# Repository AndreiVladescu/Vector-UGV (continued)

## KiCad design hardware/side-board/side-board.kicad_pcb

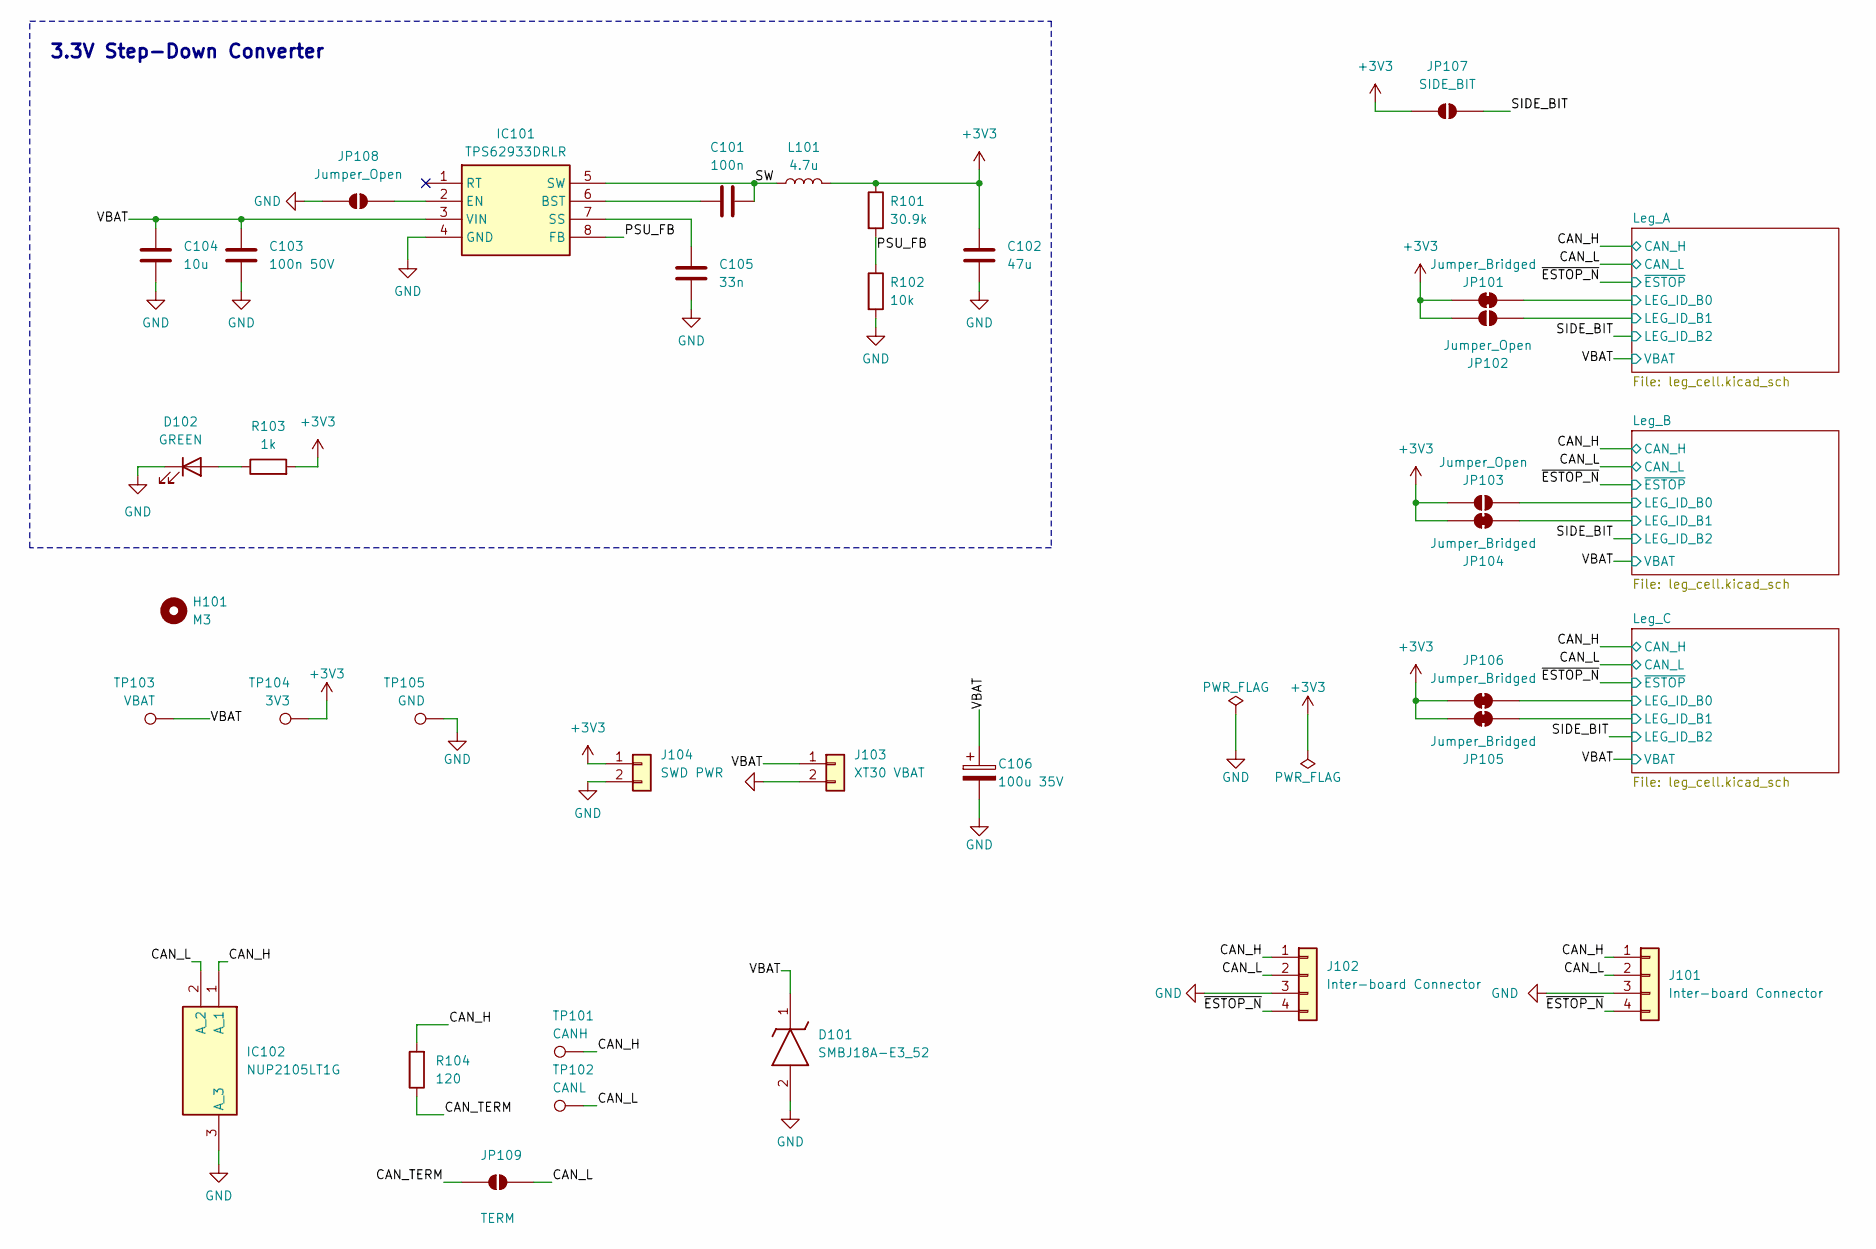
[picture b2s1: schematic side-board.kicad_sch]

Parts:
C101: 100n; C_0402_1005Metric
C102: 47u; C_0805_2012Metric
C103: 100n 50V; C_0402_1005Metric
C104: 10u; C_0603_1608Metric
C105: 33n; C_0402_1005Metric
C106: 100u 35V; CP_Elec_8x10.5
D101: SMBJ18A-E3_52; DIOM5436X244N; Mouser Part Number 625-SMBJ18A-E3
D102: GREEN; LED_0805_2012Metric
H101: M3; MountingHole_3.2mm_M3_DIN965_Pad_TopBottom
IC101: TPS62933DRLR; SOTFL50P160X60-8N; Mouser Part Number 595-TPS62933DRLR
IC102: NUP2105LT1G; SOT96P237X111-3N; Mouser Part Number 863-NUP2105LT1G
J101: Inter-board Connector; PinHeader_1x04_P2.54mm_Vertical_Tile
J102: Inter-board Connector; JST_XH_B4B-XH-A_1x04_P2.50mm_Vertical
J103: XT30 VBAT; AMASS_XT30U-M_1x02_P5.0mm_Vertical
J104: SWD PWR; PinHeader_1x02_P2.54mm_Vertical
JP101, JP104, JP105, JP106: Jumper_Bridged; SolderJumper-2_P1.3mm_Bridged2Bar_Pad1.0x1.5mm
JP102, JP103, JP108: Jumper_Open; SolderJumper-2_P1.3mm_Open_Pad1.0x1.5mm
JP107: SIDE_BIT; SolderJumper-2_P1.3mm_Open_Pad1.0x1.5mm
JP109: TERM; SolderJumper-2_P1.3mm_Open_Pad1.0x1.5mm
L101: 4.7u; INDPM4441X200N; Manufacturer_Part_Number SRP4020TA-4R7M
R101: 30.9k; R_0402_1005Metric
R102: 10k; R_0402_1005Metric
R103: 1k; R_0402_1005Metric
R104: 120; R_0402_1005Metric
TP101: CANH; TestPoint_Pad_D1.0mm
TP102: CANL; TestPoint_Pad_D1.0mm
TP103: VBAT; TestPoint_Pad_D1.0mm
TP104: 3V3; TestPoint_Pad_D1.0mm
TP105: GND; TestPoint_Pad_D1.0mm

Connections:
+3V3: C102.2, J104.1, JP101.1 (A), JP102.2 (B), JP103.1 (A), JP104.1 (A), JP105.1 (A), JP106.1 (A), JP107.1 (A), L101.2, R101.1, R103.2, TP104.1 (1_1); also elsewhere on the board
/CAN_H: IC102.1 (A_1), J101.1, J102.1, R104.2, TP101.1 (1_1); also elsewhere on the board
/CAN_L: IC102.2 (A_2), J101.2, J102.2, JP109.2 (B), TP102.1 (1_1); also elsewhere on the board
/CAN_TERM: JP109.1 (A), R104.1
/Leg_A/LEG_ID_B0: JP101.2 (B); also elsewhere on the board
/Leg_A/LEG_ID_B1: JP102.1 (A); also elsewhere on the board
/Leg_B/LEG_ID_B0: JP103.2 (B); also elsewhere on the board
/Leg_B/LEG_ID_B1: JP104.2 (B); also elsewhere on the board
/Leg_C/LEG_ID_B0: JP106.2 (B); also elsewhere on the board
/Leg_C/LEG_ID_B1: JP105.2 (B); also elsewhere on the board
/PSU_FB: IC101.8 (FB), R101.2, R102.1
/SIDE_BIT: JP107.2 (B); also elsewhere on the board
/SW: C101.2, IC101.5 (SW), L101.1
/VBAT: C103.2, C104.2, C106.1, D101.1 (K), IC101.3 (VIN), J103.1, TP103.1 (1_1); also elsewhere on the board
/~ESTOP_N: J101.4, J102.4; also elsewhere on the board
GND: C102.1, C103.1, C104.1, C105.1, C106.2, D101.2 (A), D102.1 (K), IC101.4 (GND), IC102.3 (A_3), J101.3, J102.3, J103.2, J104.2, JP108.1 (A), R102.2, TP105.1 (1_1); also elsewhere on the board
unnamed: D102.2 (A), R103.1
unnamed: C101.1, IC101.6 (BST)
unnamed: IC101.2 (EN), JP108.2 (B)
unnamed: C105.2, IC101.7 (SS)

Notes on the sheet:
3.3V Step-Down Converter

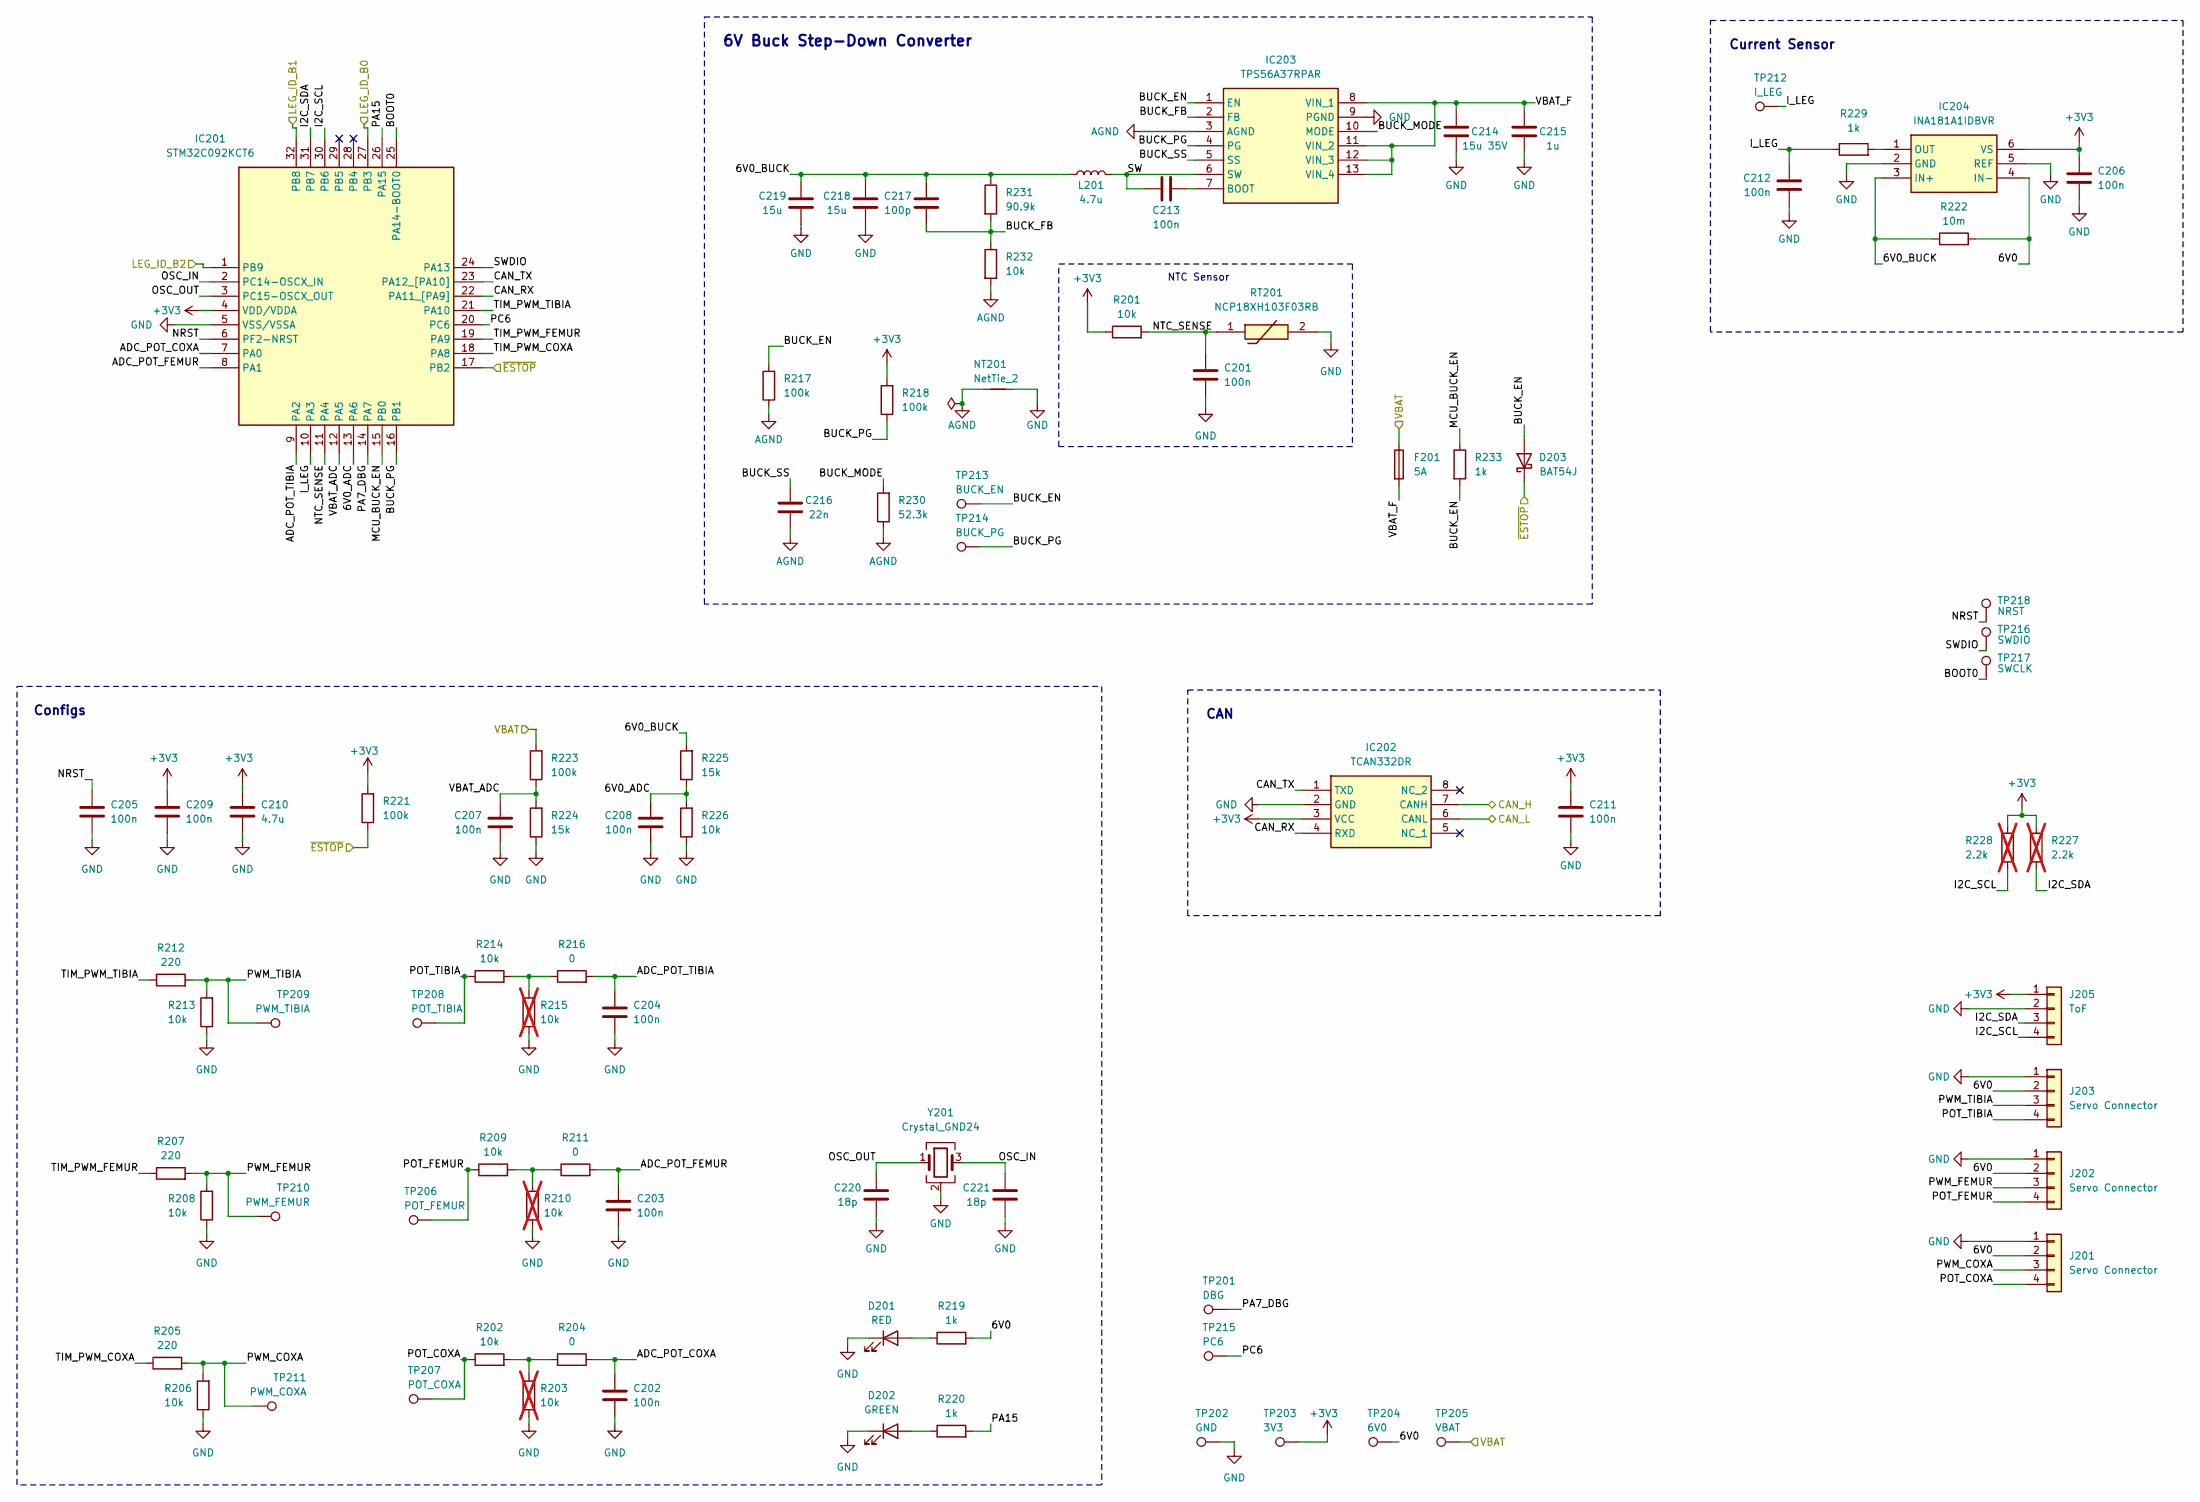
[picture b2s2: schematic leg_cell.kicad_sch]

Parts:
C201, C202, C203, C204, C205, C206, C207, C208, C209, C211, C212, C213: 100n; C_0402_1005Metric
C210: 4.7u; C_0805_2012Metric
C214: 15u 35V; C_1206_3216Metric
C215: 1u; C_0805_2012Metric
C216: 22n; C_0402_1005Metric
C217: 100p; C_0402_1005Metric
C218, C219: 15u; C_1206_3216Metric
C220, C221: 18p; C_0402_1005Metric
D201: RED; LED_0805_2012Metric
D202: GREEN; LED_0805_2012Metric
D203: BAT54J; D_SOD-323F
F201: 5A; Fuse_1206_3216Metric
IC201: STM32C092KCT6; QFP80P900X900X160-32N; Mouser Part Number 511-STM32C092KCT6
IC202: TCAN332DR; SOIC127P600X175-8N; Mouser Part Number 595-TCAN332DR
IC203: TPS56A37RPAR; Mouser Part Number 595-TPS56A37RPAR
IC204: INA181A1IDBVR; SOT95P280X145-6N; Mouser Part Number 595-INA181A1IDBVR
J201, J202, J203: Servo Connector; PinHeader_1x04_P2.54mm_Vertical_Tile
J205: ToF; PinHeader_1x04_P2.54mm_Vertical_Tile
L201: 4.7u; INDPM7973X540N; Manufacturer_Part_Number SRP7050WA-4R7M
NT201: NetTie_2; NetTie-2_SMD_Pad0.5mm
R201, R202, R206, R208, R209, R213, R214, R226, R232: 10k; R_0402_1005Metric
R203, R210, R215: 10k; R_0402_1005Metric; not fitted
R204, R211, R216: 0; R_0402_1005Metric
R205, R207, R212: 220; R_0402_1005Metric
R217, R218, R221, R223: 100k; R_0402_1005Metric
R219, R220, R229, R233: 1k; R_0402_1005Metric
R222: 10m; R_2512_6332Metric
R224, R225: 15k; R_0402_1005Metric
R227, R228: 2.2k; R_0402_1005Metric; not fitted
R230: 52.3k; R_0402_1005Metric
R231: 90.9k; R_0402_1005Metric
RT201: NCP18XH103F03RB; THRMC1608X95N; Mouser Part Number 81-NCP18XH103F03RB
TP201: DBG; TestPoint_Pad_D1.0mm
TP202: GND; TestPoint_Pad_D1.0mm
TP203: 3V3; TestPoint_Pad_D1.0mm
TP204: 6V0; TestPoint_Pad_D1.0mm
TP205: VBAT; TestPoint_Pad_D1.0mm
TP206: POT_FEMUR; TestPoint_Pad_D1.0mm
TP207: POT_COXA; TestPoint_Pad_D1.0mm
TP208: POT_TIBIA; TestPoint_Pad_D1.0mm
TP209: PWM_TIBIA; TestPoint_Pad_D1.0mm
TP210: PWM_FEMUR; TestPoint_Pad_D1.0mm
TP211: PWM_COXA; TestPoint_Pad_D1.0mm
TP212: I_LEG; TestPoint_Pad_D1.0mm
TP213: BUCK_EN; TestPoint_Pad_D1.0mm
TP214: BUCK_PG; TestPoint_Pad_D1.0mm
TP215: PC6; TestPoint_Pad_D1.0mm
TP216: SWDIO; TestPoint_Pad_D1.0mm
TP217: SWCLK; TestPoint_Pad_D1.0mm
TP218: NRST; TestPoint_Pad_D1.0mm
Y201: Crystal_GND24; Crystal_SMD_2016-4Pin_2.0x1.6mm; Manufacturer_Part_Number K2B400001210

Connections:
+3V3: C206.2, C209.2, C210.2, C211.2, IC201.4 (VDD/VDDA), IC202.3 (VCC), IC204.6 (VS), J205.1, R201.1, R218.2, R221.2, R227.2, R228.1, TP203.1 (1_1); also elsewhere on the board
/CAN_H: IC202.7 (CANH); also elsewhere on the board
/CAN_L: IC202.6 (CANL); also elsewhere on the board
/Leg_A/6V0: IC204.4 (IN-), J201.2, J202.2, J203.2, R219.2, R222.2, TP204.1 (1_1)
/Leg_A/6V0_ADC: C208.1, IC201.13 (PA6), R225.1, R226.2
/Leg_A/6V0_BUCK: C217.2, C218.2, C219.2, IC204.3 (IN+), L201.1, R222.1, R225.2, R231.1
/Leg_A/ADC_POT_COXA: C202.1, IC201.7 (PA0), R204.1
/Leg_A/ADC_POT_FEMUR: C203.1, IC201.8 (PA1), R211.2
/Leg_A/ADC_POT_TIBIA: C204.1, IC201.9 (PA2), R216.2
/Leg_A/AGND: C216.2, IC203.3 (AGND), NT201.1, R217.1, R230.1, R232.2
/Leg_A/BOOT0: IC201.25 (PA14-BOOT0), TP217.1 (1_1)
/Leg_A/BUCK_EN: D203.2 (A), IC203.1 (EN), R217.2, R233.2, TP213.1 (1_1)
/Leg_A/BUCK_FB: C217.1, IC203.2 (FB), R231.2, R232.1
/Leg_A/BUCK_MODE: IC203.10 (MODE), R230.2
/Leg_A/BUCK_PG: IC201.16 (PB1), IC203.4 (PG), R218.1, TP214.1 (1_1)
/Leg_A/BUCK_SS: C216.1, IC203.5 (SS)
/Leg_A/CAN_RX: IC201.22 (PA11_[PA9]), IC202.4 (RXD)
/Leg_A/CAN_TX: IC201.23 (PA12_[PA10]), IC202.1 (TXD)
/Leg_A/I2C_SCL: IC201.30 (PB6), J205.4, R228.2
/Leg_A/I2C_SDA: IC201.31 (PB7), J205.3, R227.1
/Leg_A/I_LEG: C212.1, IC201.10 (PA3), R229.1, TP212.1 (1_1)
/Leg_A/LEG_ID_B0: IC201.27 (PB3); also elsewhere on the board
/Leg_A/LEG_ID_B1: IC201.32 (PB8); also elsewhere on the board
/Leg_A/MCU_BUCK_EN: IC201.15 (PB0), R233.1
/Leg_A/NRST: C205.2, IC201.6 (PF2-NRST), TP218.1 (1_1)
/Leg_A/NTC_SENSE: C201.1, IC201.11 (PA4), R201.2, RT201.1
/Leg_A/OSC_IN: C221.2, IC201.2 (PC14-OSCX_IN), Y201.3
/Leg_A/OSC_OUT: C220.2, IC201.3 (PC15-OSCX_OUT), Y201.1
/Leg_A/PA7_DBG: IC201.14 (PA7), TP201.1 (1_1)
/Leg_A/PA15: IC201.26 (PA15), R220.2
/Leg_A/PC6: IC201.20 (PC6), TP215.1 (1_1)
/Leg_A/POT_COXA: J201.4, R202.1, TP207.1 (1_1)
/Leg_A/POT_FEMUR: J202.4, R209.1, TP206.1 (1_1)
/Leg_A/POT_TIBIA: J203.4, R214.1, TP208.1 (1_1)
/Leg_A/PWM_COXA: J201.3, R205.2, R206.2, TP211.1 (1_1)
/Leg_A/PWM_FEMUR: J202.3, R207.2, R208.2, TP210.1 (1_1)
/Leg_A/PWM_TIBIA: J203.3, R212.2, R213.2, TP209.1 (1_1)
/Leg_A/SW: C213.2, IC203.6 (SW), L201.2
/Leg_A/SWDIO: IC201.24 (PA13), TP216.1 (1_1)
/Leg_A/TIM_PWM_COXA: IC201.18 (PA8), R205.1
/Leg_A/TIM_PWM_FEMUR: IC201.19 (PA9), R207.1
/Leg_A/TIM_PWM_TIBIA: IC201.21 (PA10), R212.1
/Leg_A/VBAT_ADC: C207.1, IC201.12 (PA5), R223.1, R224.2
/Leg_A/VBAT_F: C214.1, C215.1, F201.2, IC203.8 (VIN_1), IC203.11 (VIN_2), IC203.12 (VIN_3), IC203.13 (VIN_4)
/SIDE_BIT: IC201.1 (PB9); also elsewhere on the board
/VBAT: F201.1, R223.2, TP205.1 (1_1); also elsewhere on the board
/~ESTOP_N: D203.1 (K), IC201.17 (PB2), R221.1; also elsewhere on the board
GND: C201.2, C202.2, C203.2, C204.2, C205.1, C206.1, C207.2, C208.2, C209.1, C210.1, C211.1, C212.2, C214.2, C215.2, C218.1, C219.1, C220.1, C221.1, D201.1 (K), D202.1 (K), IC201.5 (VSS/VSSA), IC202.2 (GND), IC203.9 (PGND), IC204.2 (GND), IC204.5 (REF), J201.1, J202.1, J203.1, J205.2, NT201.2, R203.1, R206.1, R208.1, R210.1, R213.1, R215.1, R224.1, R226.1, RT201.2, TP202.1 (1_1), Y201.2 (G), Y201.4 (G); also elsewhere on the board
unnamed: D201.2 (A), R219.1
unnamed: D202.2 (A), R220.1
unnamed: C213.1, IC203.7 (BOOT)
unnamed: IC204.1 (OUT), R229.2
unnamed: R202.2, R203.2, R204.2
unnamed: R209.2, R210.2, R211.1
unnamed: R214.2, R215.2, R216.1

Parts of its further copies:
C301, C302, C303, C304, C305, C306, C307, C308, C309, C311, C312, C313, C401, C402, C403, C404, C405, C406, C407, C408, C409, C411, C412, C413: 100n; C_0402_1005Metric
C310, C410: 4.7u; C_0805_2012Metric
C314, C414: 15u 35V; C_1206_3216Metric
C315, C415: 1u; C_0805_2012Metric
C316, C416: 22n; C_0402_1005Metric
C317, C417: 100p; C_0402_1005Metric
C318, C319, C418, C419: 15u; C_1206_3216Metric
C320, C321, C420, C421: 18p; C_0402_1005Metric
D301, D401: RED; LED_0805_2012Metric
D302, D402: GREEN; LED_0805_2012Metric
D303, D403: BAT54J; D_SOD-323F
F301, F401: 5A; Fuse_1206_3216Metric
IC301, IC401: STM32C092KCT6; QFP80P900X900X160-32N; Mouser Part Number 511-STM32C092KCT6
IC302, IC402: TCAN332DR; SOIC127P600X175-8N; Mouser Part Number 595-TCAN332DR
IC303, IC403: TPS56A37RPAR; Mouser Part Number 595-TPS56A37RPAR
IC304, IC404: INA181A1IDBVR; SOT95P280X145-6N; Mouser Part Number 595-INA181A1IDBVR
J301, J302, J303, J401, J402, J403: Servo Connector; PinHeader_1x04_P2.54mm_Vertical_Tile
J305, J405: ToF; PinHeader_1x04_P2.54mm_Vertical_Tile
L301, L401: 4.7u; INDPM7973X540N; Manufacturer_Part_Number SRP7050WA-4R7M
NT301, NT401: NetTie_2; NetTie-2_SMD_Pad0.5mm
R301, R302, R306, R308, R309, R313, R314, R326, R332, R401, R402, R406, R408, R409, R413, R414, R426, R432: 10k; R_0402_1005Metric
R303, R310, R315, R403, R410, R415: 10k; R_0402_1005Metric; not fitted
R304, R311, R316, R404, R411, R416: 0; R_0402_1005Metric
R305, R307, R312, R405, R407, R412: 220; R_0402_1005Metric
R317, R318, R321, R323, R417, R418, R421, R423: 100k; R_0402_1005Metric
R319, R320, R329, R333, R419, R420, R429, R433: 1k; R_0402_1005Metric
R322, R422: 10m; R_2512_6332Metric
R324, R325, R424, R425: 15k; R_0402_1005Metric
R327, R328, R427, R428: 2.2k; R_0402_1005Metric; not fitted
R330, R430: 52.3k; R_0402_1005Metric
R331, R431: 90.9k; R_0402_1005Metric
RT301, RT401: NCP18XH103F03RB; THRMC1608X95N; Mouser Part Number 81-NCP18XH103F03RB
TP301, TP401: DBG; TestPoint_Pad_D1.0mm
TP302, TP402: GND; TestPoint_Pad_D1.0mm
TP303, TP403: 3V3; TestPoint_Pad_D1.0mm
TP304, TP404: 6V0; TestPoint_Pad_D1.0mm
TP305, TP405: VBAT; TestPoint_Pad_D1.0mm
TP306, TP406: POT_FEMUR; TestPoint_Pad_D1.0mm
TP307, TP407: POT_COXA; TestPoint_Pad_D1.0mm
TP308, TP408: POT_TIBIA; TestPoint_Pad_D1.0mm
TP309, TP409: PWM_TIBIA; TestPoint_Pad_D1.0mm
TP310, TP410: PWM_FEMUR; TestPoint_Pad_D1.0mm
TP311, TP411: PWM_COXA; TestPoint_Pad_D1.0mm
TP312, TP412: I_LEG; TestPoint_Pad_D1.0mm
TP313, TP413: BUCK_EN; TestPoint_Pad_D1.0mm
TP314, TP414: BUCK_PG; TestPoint_Pad_D1.0mm
TP315, TP415: PC6; TestPoint_Pad_D1.0mm
TP316, TP416: SWDIO; TestPoint_Pad_D1.0mm
TP317, TP417: SWCLK; TestPoint_Pad_D1.0mm
TP318, TP418: NRST; TestPoint_Pad_D1.0mm
Y301, Y401: Crystal_GND24; Crystal_SMD_2016-4Pin_2.0x1.6mm; Manufacturer_Part_Number K2B400001210

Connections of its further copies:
+3V3: C306.2, C309.2, C310.2, C311.2, C406.2, C409.2, C410.2, C411.2, IC301.4 (VDD/VDDA), IC302.3 (VCC), IC304.6 (VS), IC401.4 (VDD/VDDA), IC402.3 (VCC), IC404.6 (VS), J305.1, J405.1, R301.1, R318.2, R321.2, R327.2, R328.1, R401.1, R418.2, R421.2, R427.2, R428.1, TP303.1 (1_1), TP403.1 (1_1); also elsewhere on the board
/CAN_H: IC302.7 (CANH), IC402.7 (CANH); also elsewhere on the board
/CAN_L: IC302.6 (CANL), IC402.6 (CANL); also elsewhere on the board
/Leg_B/6V0: IC304.4 (IN-), J301.2, J302.2, J303.2, R319.2, R322.2, TP304.1 (1_1)
/Leg_B/6V0_ADC: C308.1, IC301.13 (PA6), R325.1, R326.2
/Leg_B/6V0_BUCK: C317.2, C318.2, C319.2, IC304.3 (IN+), L301.1, R322.1, R325.2, R331.1
/Leg_B/ADC_POT_COXA: C302.1, IC301.7 (PA0), R304.1
/Leg_B/ADC_POT_FEMUR: C303.1, IC301.8 (PA1), R311.2
/Leg_B/ADC_POT_TIBIA: C304.1, IC301.9 (PA2), R316.2
/Leg_B/AGND: C316.2, IC303.3 (AGND), NT301.1, R317.1, R330.1, R332.2
/Leg_B/BOOT0: IC301.25 (PA14-BOOT0), TP317.1 (1_1)
/Leg_B/BUCK_EN: D303.2 (A), IC303.1 (EN), R317.2, R333.2, TP313.1 (1_1)
/Leg_B/BUCK_FB: C317.1, IC303.2 (FB), R331.2, R332.1
/Leg_B/BUCK_MODE: IC303.10 (MODE), R330.2
/Leg_B/BUCK_PG: IC301.16 (PB1), IC303.4 (PG), R318.1, TP314.1 (1_1)
/Leg_B/BUCK_SS: C316.1, IC303.5 (SS)
/Leg_B/CAN_RX: IC301.22 (PA11_[PA9]), IC302.4 (RXD)
/Leg_B/CAN_TX: IC301.23 (PA12_[PA10]), IC302.1 (TXD)
/Leg_B/I2C_SCL: IC301.30 (PB6), J305.4, R328.2
/Leg_B/I2C_SDA: IC301.31 (PB7), J305.3, R327.1
/Leg_B/I_LEG: C312.1, IC301.10 (PA3), R329.1, TP312.1 (1_1)
/Leg_B/LEG_ID_B0: IC301.27 (PB3); also elsewhere on the board
/Leg_B/LEG_ID_B1: IC301.32 (PB8); also elsewhere on the board
/Leg_B/MCU_BUCK_EN: IC301.15 (PB0), R333.1
/Leg_B/NRST: C305.2, IC301.6 (PF2-NRST), TP318.1 (1_1)
/Leg_B/NTC_SENSE: C301.1, IC301.11 (PA4), R301.2, RT301.1
/Leg_B/OSC_IN: C321.2, IC301.2 (PC14-OSCX_IN), Y301.3
/Leg_B/OSC_OUT: C320.2, IC301.3 (PC15-OSCX_OUT), Y301.1
/Leg_B/PA7_DBG: IC301.14 (PA7), TP301.1 (1_1)
/Leg_B/PA15: IC301.26 (PA15), R320.2
/Leg_B/PC6: IC301.20 (PC6), TP315.1 (1_1)
/Leg_B/POT_COXA: J301.4, R302.1, TP307.1 (1_1)
/Leg_B/POT_FEMUR: J302.4, R309.1, TP306.1 (1_1)
/Leg_B/POT_TIBIA: J303.4, R314.1, TP308.1 (1_1)
/Leg_B/PWM_COXA: J301.3, R305.2, R306.2, TP311.1 (1_1)
/Leg_B/PWM_FEMUR: J302.3, R307.2, R308.2, TP310.1 (1_1)
/Leg_B/PWM_TIBIA: J303.3, R312.2, R313.2, TP309.1 (1_1)
/Leg_B/SW: C313.2, IC303.6 (SW), L301.2
/Leg_B/SWDIO: IC301.24 (PA13), TP316.1 (1_1)
/Leg_B/TIM_PWM_COXA: IC301.18 (PA8), R305.1
/Leg_B/TIM_PWM_FEMUR: IC301.19 (PA9), R307.1
/Leg_B/TIM_PWM_TIBIA: IC301.21 (PA10), R312.1
/Leg_B/VBAT_ADC: C307.1, IC301.12 (PA5), R323.1, R324.2
/Leg_B/VBAT_F: C314.1, C315.1, F301.2, IC303.8 (VIN_1), IC303.11 (VIN_2), IC303.12 (VIN_3), IC303.13 (VIN_4)
/Leg_C/6V0: IC404.4 (IN-), J401.2, J402.2, J403.2, R419.2, R422.2, TP404.1 (1_1)
/Leg_C/6V0_ADC: C408.1, IC401.13 (PA6), R425.1, R426.2
/Leg_C/6V0_BUCK: C417.2, C418.2, C419.2, IC404.3 (IN+), L401.1, R422.1, R425.2, R431.1
/Leg_C/ADC_POT_COXA: C402.1, IC401.7 (PA0), R404.1
/Leg_C/ADC_POT_FEMUR: C403.1, IC401.8 (PA1), R411.2
/Leg_C/ADC_POT_TIBIA: C404.1, IC401.9 (PA2), R416.2
/Leg_C/AGND: C416.2, IC403.3 (AGND), NT401.1, R417.1, R430.1, R432.2
/Leg_C/BOOT0: IC401.25 (PA14-BOOT0), TP417.1 (1_1)
/Leg_C/BUCK_EN: D403.2 (A), IC403.1 (EN), R417.2, R433.2, TP413.1 (1_1)
/Leg_C/BUCK_FB: C417.1, IC403.2 (FB), R431.2, R432.1
/Leg_C/BUCK_MODE: IC403.10 (MODE), R430.2
/Leg_C/BUCK_PG: IC401.16 (PB1), IC403.4 (PG), R418.1, TP414.1 (1_1)
/Leg_C/BUCK_SS: C416.1, IC403.5 (SS)
/Leg_C/CAN_RX: IC401.22 (PA11_[PA9]), IC402.4 (RXD)
/Leg_C/CAN_TX: IC401.23 (PA12_[PA10]), IC402.1 (TXD)
/Leg_C/I2C_SCL: IC401.30 (PB6), J405.4, R428.2
/Leg_C/I2C_SDA: IC401.31 (PB7), J405.3, R427.1
/Leg_C/I_LEG: C412.1, IC401.10 (PA3), R429.1, TP412.1 (1_1)
/Leg_C/LEG_ID_B0: IC401.27 (PB3); also elsewhere on the board
/Leg_C/LEG_ID_B1: IC401.32 (PB8); also elsewhere on the board
/Leg_C/MCU_BUCK_EN: IC401.15 (PB0), R433.1
/Leg_C/NRST: C405.2, IC401.6 (PF2-NRST), TP418.1 (1_1)
/Leg_C/NTC_SENSE: C401.1, IC401.11 (PA4), R401.2, RT401.1
/Leg_C/OSC_IN: C421.2, IC401.2 (PC14-OSCX_IN), Y401.3
/Leg_C/OSC_OUT: C420.2, IC401.3 (PC15-OSCX_OUT), Y401.1
/Leg_C/PA7_DBG: IC401.14 (PA7), TP401.1 (1_1)
/Leg_C/PA15: IC401.26 (PA15), R420.2
/Leg_C/PC6: IC401.20 (PC6), TP415.1 (1_1)
/Leg_C/POT_COXA: J401.4, R402.1, TP407.1 (1_1)
/Leg_C/POT_FEMUR: J402.4, R409.1, TP406.1 (1_1)
/Leg_C/POT_TIBIA: J403.4, R414.1, TP408.1 (1_1)
/Leg_C/PWM_COXA: J401.3, R405.2, R406.2, TP411.1 (1_1)
/Leg_C/PWM_FEMUR: J402.3, R407.2, R408.2, TP410.1 (1_1)
/Leg_C/PWM_TIBIA: J403.3, R412.2, R413.2, TP409.1 (1_1)
/Leg_C/SW: C413.2, IC403.6 (SW), L401.2
/Leg_C/SWDIO: IC401.24 (PA13), TP416.1 (1_1)
/Leg_C/TIM_PWM_COXA: IC401.18 (PA8), R405.1
/Leg_C/TIM_PWM_FEMUR: IC401.19 (PA9), R407.1
/Leg_C/TIM_PWM_TIBIA: IC401.21 (PA10), R412.1
/Leg_C/VBAT_ADC: C407.1, IC401.12 (PA5), R423.1, R424.2
/Leg_C/VBAT_F: C414.1, C415.1, F401.2, IC403.8 (VIN_1), IC403.11 (VIN_2), IC403.12 (VIN_3), IC403.13 (VIN_4)
/SIDE_BIT: IC301.1 (PB9), IC401.1 (PB9); also elsewhere on the board
/VBAT: F301.1, F401.1, R323.2, R423.2, TP305.1 (1_1), TP405.1 (1_1); also elsewhere on the board
/~ESTOP_N: D303.1 (K), D403.1 (K), IC301.17 (PB2), IC401.17 (PB2), R321.1, R421.1; also elsewhere on the board
GND: C301.2, C302.2, C303.2, C304.2, C305.1, C306.1, C307.2, C308.2, C309.1, C310.1, C311.1, C312.2, C314.2, C315.2, C318.1, C319.1, C320.1, C321.1, C401.2, C402.2, C403.2, C404.2, C405.1, C406.1, C407.2, C408.2, C409.1, C410.1, C411.1, C412.2, C414.2, C415.2, C418.1, C419.1, C420.1, C421.1, D301.1 (K), D302.1 (K), D401.1 (K), D402.1 (K), IC301.5 (VSS/VSSA), IC302.2 (GND), IC303.9 (PGND), IC304.2 (GND), IC304.5 (REF), IC401.5 (VSS/VSSA), IC402.2 (GND), IC403.9 (PGND), IC404.2 (GND), IC404.5 (REF), J301.1, J302.1, J303.1, J305.2, J401.1, J402.1, J403.1, J405.2, NT301.2, NT401.2, R303.1, R306.1, R308.1, R310.1, R313.1, R315.1, R324.1, R326.1, R403.1, R406.1, R408.1, R410.1, R413.1, R415.1, R424.1, R426.1, RT301.2, RT401.2, TP302.1 (1_1), TP402.1 (1_1), Y301.2 (G), Y301.4 (G), Y401.2 (G), Y401.4 (G); also elsewhere on the board
unnamed: D301.2 (A), R319.1
unnamed: D302.2 (A), R320.1
unnamed: D401.2 (A), R419.1
unnamed: D402.2 (A), R420.1
unnamed: C313.1, IC303.7 (BOOT)
unnamed: IC304.1 (OUT), R329.2
unnamed: C413.1, IC403.7 (BOOT)
unnamed: IC404.1 (OUT), R429.2
unnamed: R302.2, R303.2, R304.2
unnamed: R309.2, R310.2, R311.1
unnamed: R314.2, R315.2, R316.1
unnamed: R402.2, R403.2, R404.2
unnamed: R409.2, R410.2, R411.1
unnamed: R414.2, R415.2, R416.1

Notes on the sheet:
6V Buck Step-Down Converter
CAN
Configs
Current Sensor
NTC Sensor

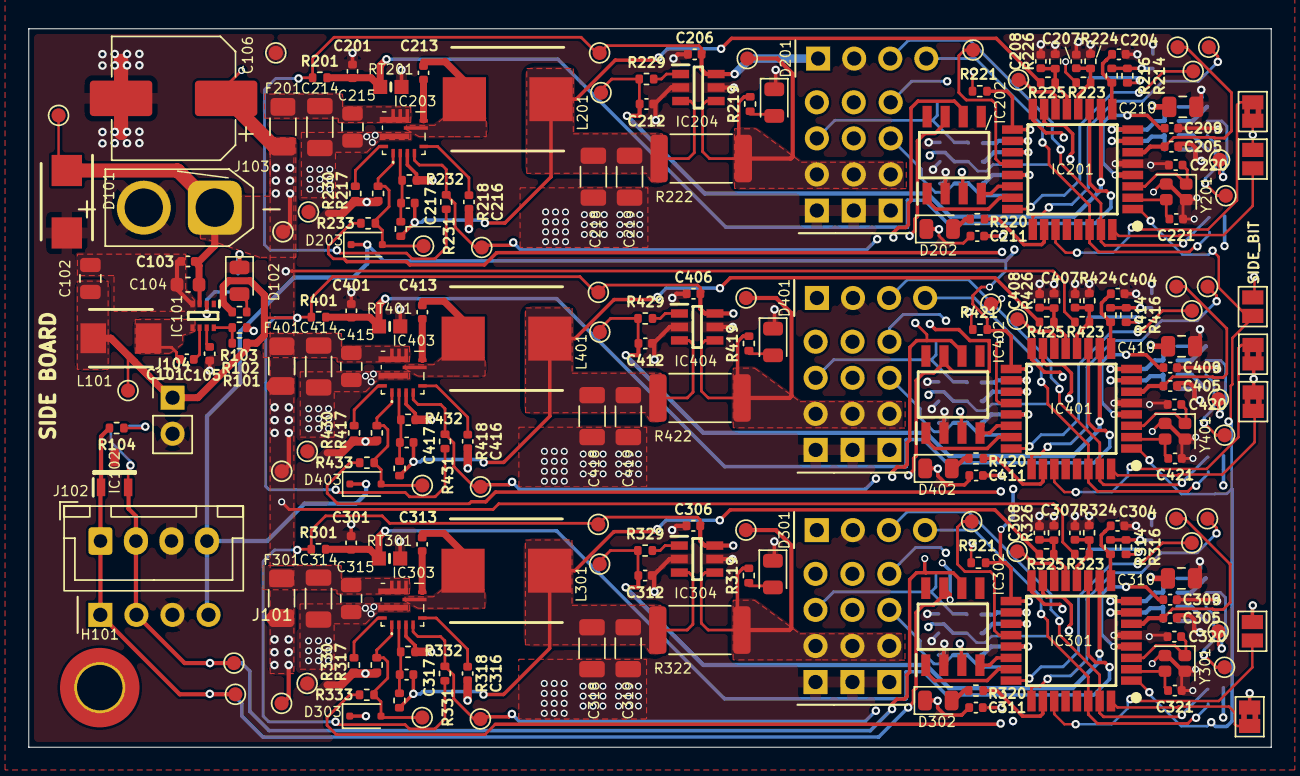
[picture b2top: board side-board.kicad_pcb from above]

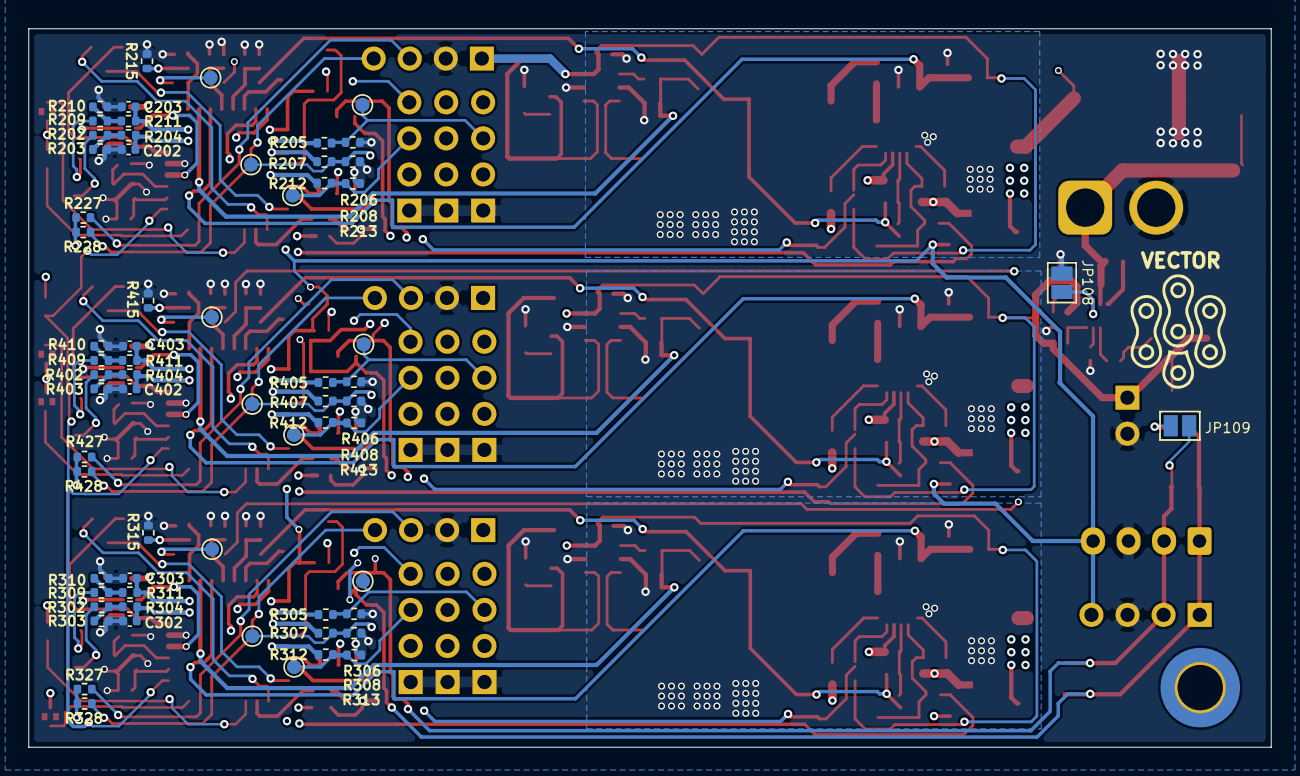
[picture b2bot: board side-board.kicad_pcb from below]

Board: 4 copper layers, 87.5 x 50.6 mm, 298 parts (65 on the bottom side), 158 nets.
